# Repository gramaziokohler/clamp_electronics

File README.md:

# clamp_electronics
Electronics for remote controlled robotic actuators (clamps). 

This repo is part of the [Robotic Assembled Timber Structures with Integral Timber Joints](https://github.com/gramaziokohler/integral_timber_joints) project. 

## Repo folder structure

This repository hold the following files:

- **/xx_Description** - Eagle schematics and board designs for a specific controller design
- **/eagle_library** - stores custom eagle libraries from third-party or created by myself
- **/doc** - Electronics modules and other components documentation from original manufactures.

## Design Goals

The goal of the clamp controller is to be able to achieve the following high-level functions: 

- Communicate wirelessly with a radio base station
  - Receive commands
  - Report status
  - Report a jammed stop during move
- Control 1 or 2 motors for the clamp's main linear movement
  - Positional Control
  - Follow a trapezoidal motion profile
- Operate on 3 or 4-cell Li-Po Battery power
- Monitor jamming conditions of the clamp
- Monitor sensors (if any, such as loadcells)
- Monitor end / homing switch
- Monitor pneumatic autoswitch
- Monitor battery voltage

## Controller Design

Not all designs implemented the full list of design goals.

### [01_SerialController](/01_SerialController/01_SerialController.md)

This controller receives command from Serial Tx Rx pins.

Two load cell can be connected via two HX711 Analog-to_Digital Module.

The design supports two DC motors with *single* channel encoder. The shaft rotation direction is inferred from the direction of programmed movement. (This design is later proved to be imprecise)

### [02_RadioPIDController](02_RadioPIDController/02_RadioPIDController.md)

This controller interfaces the CC1101 radio directly via Hardware SPI on Arduino Nano. It can receive and respond to commands from either USB Serial or from the Radio.

The hardware and pin out supports two motors being PID controlled with two-channel encoder feedback.

### [03_RadioPIDControllerV2](03_RadioPIDControllerV2/03_RadioPIDControllerV2.md)

This controller is an improvement of the 02_RadioPIDController with the intent to improve the following aspects:

- Better DC power regulation to avoid digital blackout
- Ability to support a two-motor firmware or single-motor (with added features) firmware.
- 1 or 2 LED output with onboard series resistor

### [10_ESP32CAMAdapter](10_ESP32CAMAdapter/10_ESP32CAMAdapter.md)

This an adapter board for connecting AIThinker ESP32-CAM module.

## Sub-systems and Electronic Module Documentation

### Motor Driver

[Motor Driver XY160D](doc/motor_driver/motor_driver_XY160D.md)

This H-Bridge Bi-Directional MOSFET motor driver is chosen due to its high rated current (7A constant, 50A peak).  

- Other drivers such as L298N offers low output current (L298N only 2A constant output 3A peak per channel) 
- This driver has a simple IN1 + IN2 + ENA interface which is easy to interface. 
- PWM and Bidirectional operation is necessary for position control.

### Radio

[Details of CC1101 Radio Module](doc/radio/CC1101_Radio.md)

This CC1101 radio module is chosen because it is the most available sub-GHz packet based radio.

- The sub-GHz frequency is better at going around obstacles in a construction environment.
- ISM bands that are free to use.
- The highly integrated radio transceiver chip on a module is easy to use and interface. 
- Existing Arduino compatible library exists.

Radio frequency / channel / sync word and it's operation is controlled by software and are documented in firmware repo.

### MCU

The Arduino Nano (ATmega328 + new bootloader) is chosen for its small size, low cost and protoboard friendly pin layout. The Nano do not have a lot of IO available but is barely enough for a 2 motor controller.

[Arduino Nano V3 Pinout](http://lab.dejaworks.com/arduino-nano-pinouts/) ( [Arduino.cc Nano Page](https://store.arduino.cc/arduino-nano) )

### Load Cell

A 4-wire load cell can be used to dynamically measure the pull force of the actuator. Such load cell can be interfaced to the Arduino via a AD Converter designed for load cell measurement.

[Details of the HX711 Load Cell A/D Module](/doc/load_cell/load_cell.md)

The HX711 module was selected due to its compact size, low cost and ready-to-use library. Measuring frequency is 80Hz.

### Battery Voltage Regulation for controller

The fluctuating battery voltage for a 4-cell Li-Po is between 12.8V to 16.8V. This needs to be regulated to stable 5V DC for the digital circuitry.

[Details and calculation of LM7805 option](doc/voltage_regulation/linear_regulator.md)

### Battery Voltage Sense

[Details and calculation of voltage divider](doc/battery_sense/Battery_Voltage_Sensing.md)

### Battery Cable Harness

A Y cable is necessary to connect the Li-Po Battery to both the motor driver and the controller Battery. 

**Male XT60 Connector** at the battery side

**2x Female Phoenix Terminal Block Plug** (Phoenix 1757019 - MSTB 5.08 picth) at controller side.

------

## Peripheral Devices

The choice of DC motor and Li-Po Battery is flexible from the perspective of the controller electronics. As long as their specification is within allowable range defined below:

### DC Motor

The chosen DC motor should be rated 12V. Other ratings might work as long as overheat is not an issue and sufficient torque is produced.

### Hall Effect Sensor

Two phase hall effect shaft encoder should be used for positional feedback. The output of the encoder should ideally be 5V TTL logic. 

Should the motor have a gearbox, the shaft encoder should be attached to the motor shaft (not the gearbox output shaft) for better resolution.

Sensor resolution should be around 500 - 1000 steps per 1mm clamp linear output.

### Li-Po Battery

**4-cell** Li-Po battery is chosen for the following reasons:

- High power density for starting DC motor
- High energy density to save space and weight
- 14.8V - 16.8V voltage match well with 12V DC motor.

**1000mAh** or above for reasonable use time.

**XT60 Connector** is conventional

**Voltage Assumption for calculation**: We assume a fully charged 4-cell battery to have **16.8V (@4.2V)**, and stop using the battery at **14.8V (@3.7V)**  , although absolute minimum is **14.0V (@3.5V)**

Note: 3-cell battery will also operate fine but at reduced torque

Credits
-------------

This repository was created by Pok Yin Victor Leung <leung@arch.ethz.ch> [@yck011522 ](https://github.com/yck011522) at [@gramaziokohler](https://github.com/gramaziokohler)

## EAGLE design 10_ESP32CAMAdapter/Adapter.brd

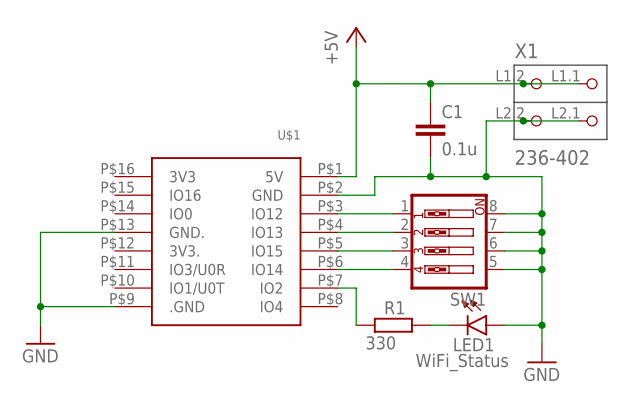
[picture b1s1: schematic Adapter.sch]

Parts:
C1: 0.1u; C050-030X075
LED1: WiFi_Status; LED3MM
R1: 330; 0204V
SW1: SW_DIP-4; EDG-04
U$1: ESP32-CAM
X1: 236-402; P-236-402

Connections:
+5V: C1.1, U$1.P$1 (5V), X1.L1.1 (P1.1), X1.L1.2 (P1.2)
GND: C1.2, LED1.A, SW1.5, SW1.6, SW1.7, SW1.8, U$1.P$2 (GND), U$1.P$9 (.GND), U$1.P$13 (GND.), X1.L2.1 (P2.1), X1.L2.2 (P2.2)
unnamed: SW1.1, U$1.P$3 (IO12)
unnamed: SW1.2, U$1.P$4 (IO13)
unnamed: SW1.3, U$1.P$5 (IO15)
unnamed: SW1.4, U$1.P$6 (IO14)
unnamed: R1.1, U$1.P$7 (IO2)
unnamed: LED1.K (C), R1.2

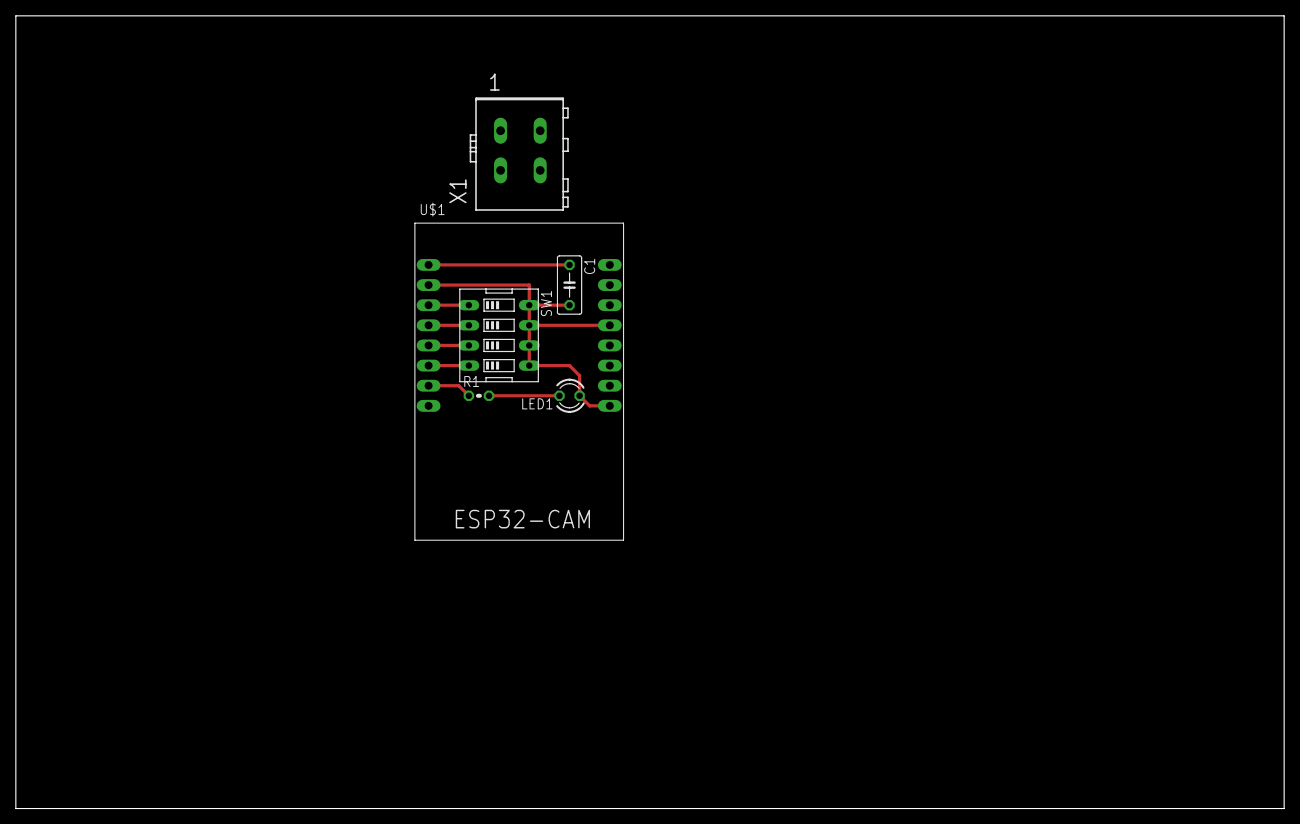
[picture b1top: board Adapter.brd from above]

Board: 2 copper layers, 160.0 x 100.0 mm, 6 parts (0 on the bottom side), 8 nets.

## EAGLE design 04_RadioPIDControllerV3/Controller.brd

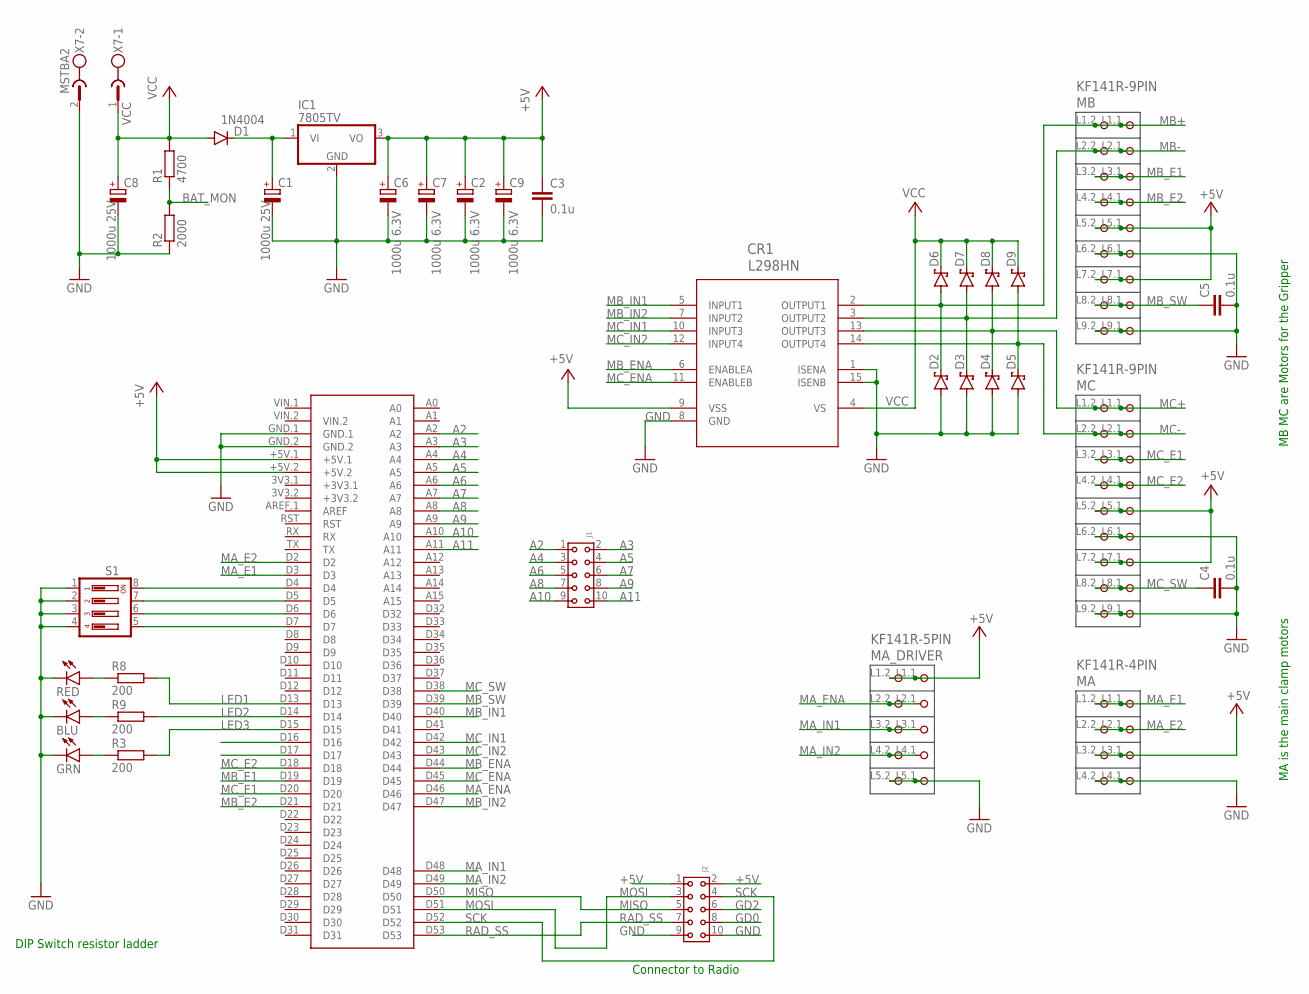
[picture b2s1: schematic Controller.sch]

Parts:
BLU: LED5MM
C1, C8: 1000u 25V; E3,5-10
C2, C6, C7, C9: 1000u 6.3V; E4-8-13HORI
C3, C4, C5: 0.1u; C050-030X075
CR1: L298HN; MULTIWATT15_H_STM
D1: 1N4004; DO41-10
D2, D3, D4, D5, D6, D7, D8, D9: 1N5819-B; DO41-7.6
GRN: LED5MM
IC1: 7805TV; TO220V
J1, J2: 6130XX21821_61301021821; 61301021821
MA: KF141R-4PIN
MA_DRIVER: KF141R-5PIN
MB: KF141R-9PIN
MC: KF141R-9PIN
R1: 4700; 0207/7
R2: 2000; 0207/7
R3, R8, R9: 200; 0207/7
RED: LED5MM
S1: DIP04YL
U$1: MEGA2560_MIKRO
X7: MSTBA2

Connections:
+5V: C2.+, C3.1, C6.+, C7.+, C9.+, CR1.9 (VSS), IC1.3 (VO), J2.1, J2.2, MA.L3.1 (P3.1), MA.L3.2 (P3.2), MA_DRIVER.L1.1 (P1.1), MA_DRIVER.L1.2 (P1.2), MB.L5.1 (P5.1), MB.L5.2 (P5.2), MB.L7.1 (P7.1), MB.L7.2 (P7.2), MC.L5.1 (P5.1), MC.L5.2 (P5.2), MC.L7.1 (P7.1), MC.L7.2 (P7.2), U$1.+5V.1, U$1.+5V.2
A2: J1.1, U$1.A2
A3: J1.2, U$1.A3
A4: J1.3, U$1.A4
A5: J1.4, U$1.A5
A6: J1.5, U$1.A6
A7: J1.6, U$1.A7
A8: J1.7, U$1.A8
A9: J1.8, U$1.A9
A10: J1.9, U$1.A10
A11: J1.10, U$1.A11
BAT_MON: R1.1, R2.2
GD0: J2.8
GD2: J2.6
GND: BLU.K (C), C1.-, C2.-, C3.2, C4.2, C5.2, C6.-, C7.-, C8.-, C9.-, CR1.1 (ISENA), CR1.8 (GND), CR1.15 (ISENB), D2.A, D3.A, D4.A, D5.A, GRN.K (C), IC1.2 (GND), J2.9, J2.10, MA.L4.1 (P4.1), MA.L4.2 (P4.2), MA_DRIVER.L5.1 (P5.1), MA_DRIVER.L5.2 (P5.2), MB.L6.1 (P6.1), MB.L6.2 (P6.2), MB.L9.1 (P9.1), MB.L9.2 (P9.2), MC.L6.1 (P6.1), MC.L6.2 (P6.2), MC.L9.1 (P9.1), MC.L9.2 (P9.2), R2.1, RED.K (C), S1.1, S1.2, S1.3, S1.4, U$1.GND.1, U$1.GND.2, X7.2
LED1: R8.2, U$1.D13
LED2: R9.2, U$1.D14
LED3: R3.2, U$1.D15
MA_E1: MA.L1.1 (P1.1), MA.L1.2 (P1.2), U$1.D3
MA_E2: MA.L2.1 (P2.1), MA.L2.2 (P2.2), U$1.D2
MA_ENA: MA_DRIVER.L2.1 (P2.1), MA_DRIVER.L2.2 (P2.2), U$1.D46
MA_IN1: MA_DRIVER.L3.1 (P3.1), MA_DRIVER.L3.2 (P3.2), U$1.D48
MA_IN2: MA_DRIVER.L4.1 (P4.1), MA_DRIVER.L4.2 (P4.2), U$1.D49
MB+: CR1.2 (OUTPUT1), D2.C, D6.A, MB.L1.1 (P1.1), MB.L1.2 (P1.2)
MB-: CR1.3 (OUTPUT2), D3.C, D7.A, MB.L2.1 (P2.1), MB.L2.2 (P2.2)
MB_E1: MB.L3.1 (P3.1), MB.L3.2 (P3.2), U$1.D19
MB_E2: MB.L4.1 (P4.1), MB.L4.2 (P4.2), U$1.D21
MB_ENA: CR1.6 (ENABLEA), U$1.D44
MB_IN1: CR1.5 (INPUT1), U$1.D40
MB_IN2: CR1.7 (INPUT2), U$1.D47
MB_SW: C5.1, MB.L8.1 (P8.1), MB.L8.2 (P8.2), U$1.D39
MC+: CR1.13 (OUTPUT3), D4.C, D8.A, MC.L1.1 (P1.1), MC.L1.2 (P1.2)
MC-: CR1.14 (OUTPUT4), D5.C, D9.A, MC.L2.1 (P2.1), MC.L2.2 (P2.2)
MC_E1: MC.L3.1 (P3.1), MC.L3.2 (P3.2), U$1.D20
MC_E2: MC.L4.1 (P4.1), MC.L4.2 (P4.2), U$1.D18
MC_ENA: CR1.11 (ENABLEB), U$1.D45
MC_IN1: CR1.10 (INPUT3), U$1.D42
MC_IN2: CR1.12 (INPUT4), U$1.D43
MC_SW: C4.1, MC.L8.1 (P8.1), MC.L8.2 (P8.2), U$1.D38
MISO: J2.5, U$1.D50
MOSI: J2.3, U$1.D51
unnamed: C1.+, D1.C, IC1.1 (VI)
unnamed: R8.1, RED.A
unnamed: BLU.A, R9.1
unnamed: GRN.A, R3.1
unnamed: S1.8, U$1.D4
unnamed: S1.7, U$1.D5
unnamed: S1.6, U$1.D6
unnamed: S1.5, U$1.D7
RAD_SS: J2.7, U$1.D53
SCK: J2.4, U$1.D52
VCC: C8.+, CR1.4 (VS), D1.A, D6.C, D7.C, D8.C, D9.C, R1.2, X7.1

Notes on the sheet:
Connector to Radio
DIP Switch resistor ladder
MB MC are Motors for the Gripper
MA is the main clamp motors

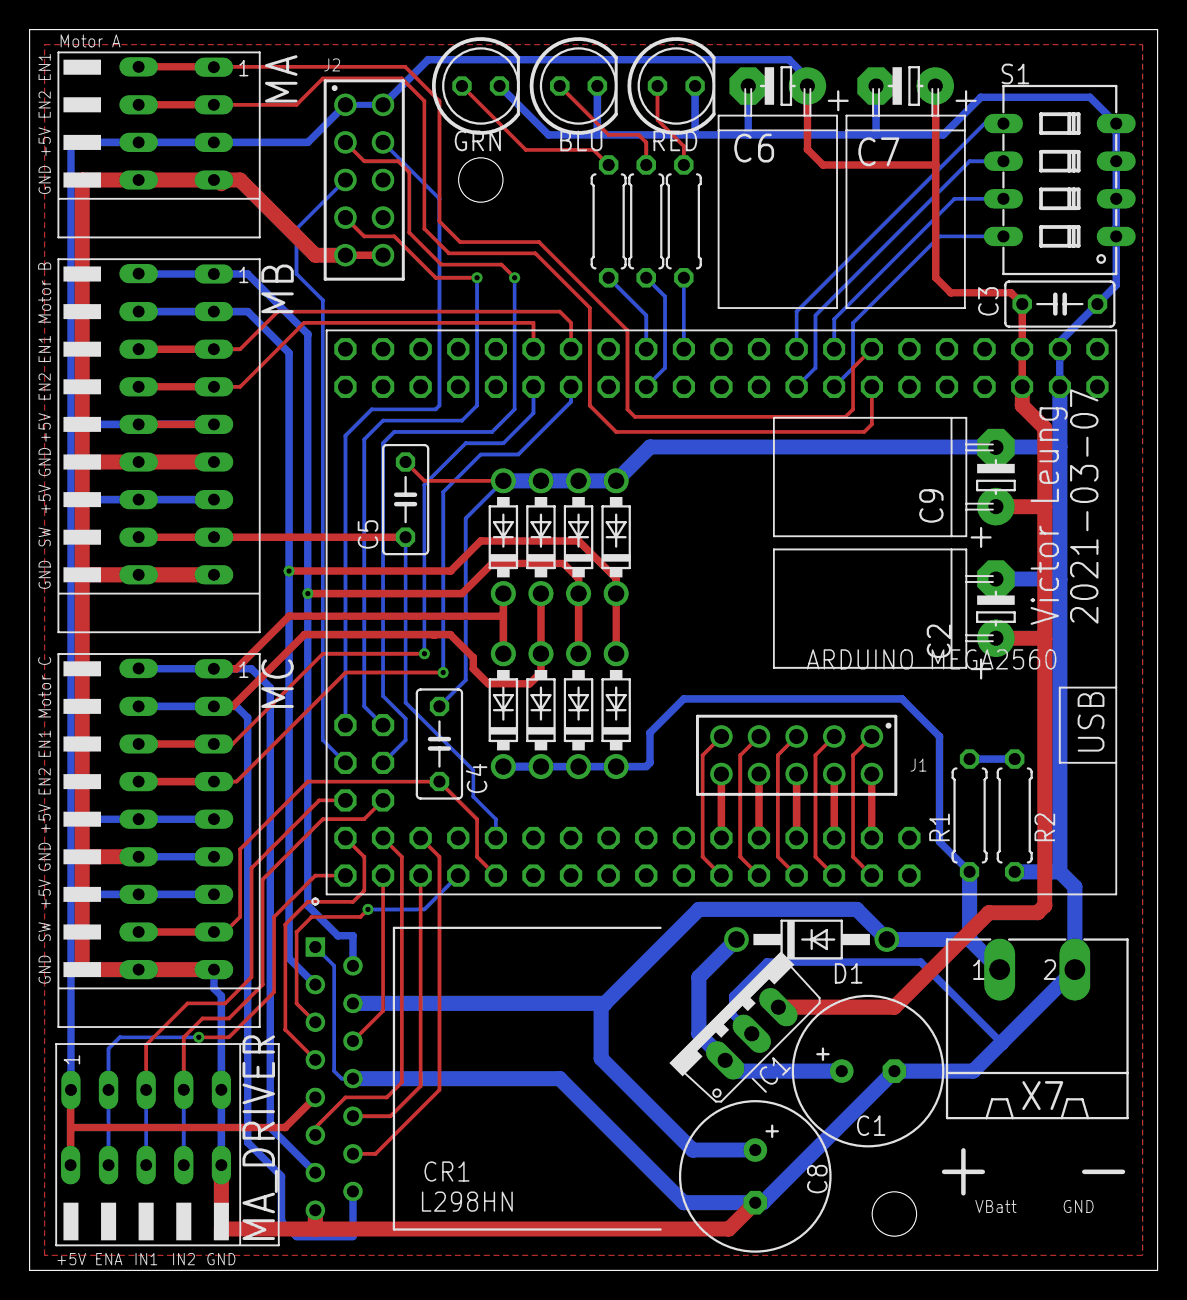
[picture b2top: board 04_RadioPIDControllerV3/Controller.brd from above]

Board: 2 copper layers, 76.2 x 83.8 mm, 37 parts (0 on the bottom side), 50 nets.

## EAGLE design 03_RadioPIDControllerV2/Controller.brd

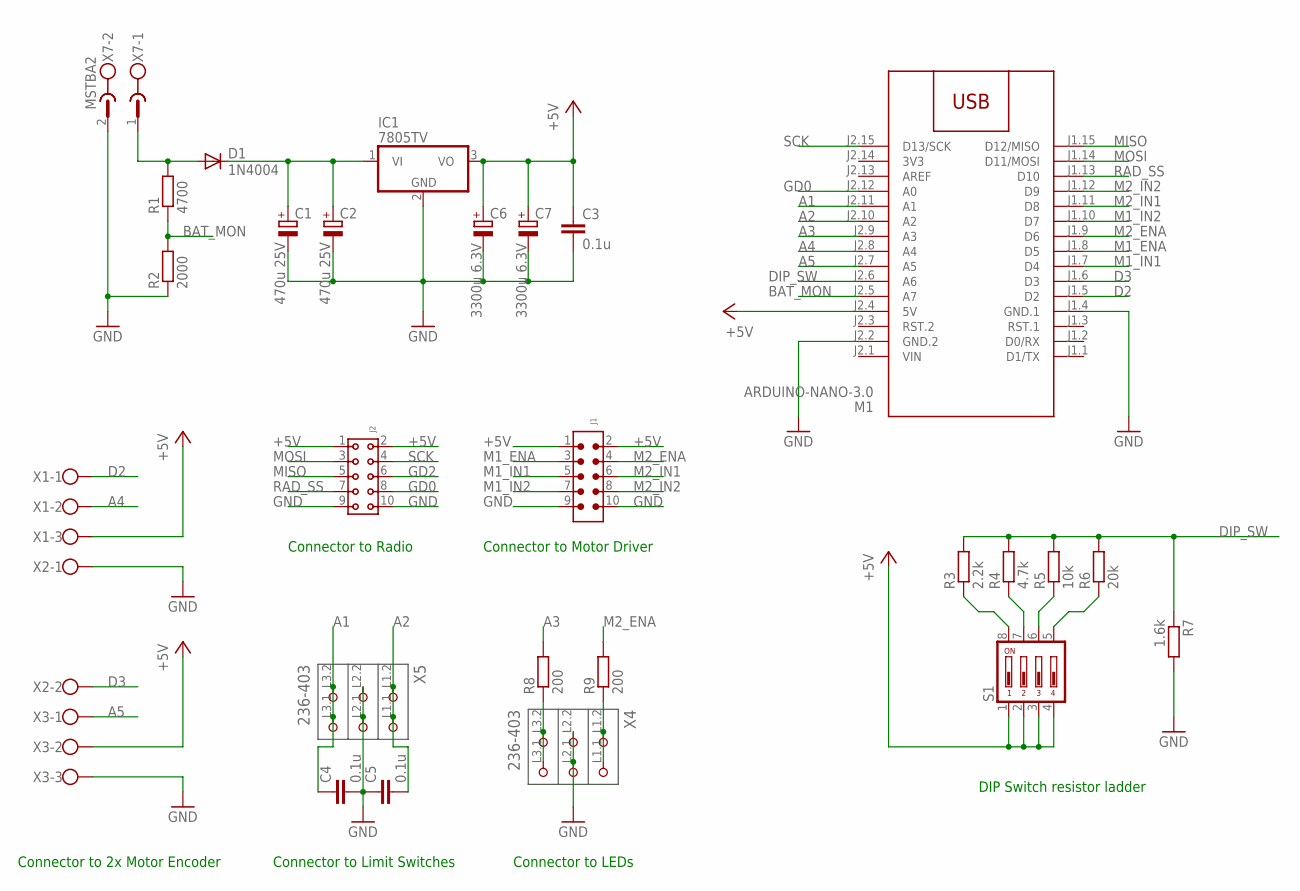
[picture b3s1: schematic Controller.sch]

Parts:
C1, C2: 470u 25V; E3,5-8
C3, C4, C5: 0.1u; C050-030X075
C6, C7: 3300u 6.3V; E3,5-10
D1: 1N4004; DO41-10
IC1: 7805TV; TO220V
J1: 6120XX21621_61201021621; 61201021621
J2: 6130XX21821_61301021821; 61301021821
M1: ARDUINO-NANO-3.0
R1: 4700; 0207/10
R2: 2000; 0207/7
R3: 2.2k; 0207/10
R4: 4.7k; 0207/10
R5: 10k; 0207/10
R6: 20k; 0207/10
R7: 1.6k; 0207/10
R8: 200; 0207/12
R9: 200; 0207/15
S1: DIP04YL
X1, X3: W237-103
X2: W237-102
X4, X5: 236-403; P-236-403
X7: MSTBA2

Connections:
3V3: M1.J2.14 (3V3)
+5V: C3.1, C6.+, C7.+, IC1.3 (VO), J1.1, J1.2, J2.1, J2.2, M1.J2.4 (5V), S1.1, S1.2, S1.3, S1.4, X1.3, X3.2
A1: C4.1, M1.J2.11 (A1), X5.L3.1 (P3.1), X5.L3.2 (P3.2)
A2: C5.2, M1.J2.10 (A2), X5.L1.1 (P1.1), X5.L1.2 (P1.2)
A3: M1.J2.9 (A3), R8.2
A4: M1.J2.8 (A4), X1.2
A5: M1.J2.7 (A5), X3.1
BAT_MON: M1.J2.5 (A7), R1.1, R2.2
D2: M1.J1.5 (D2), X1.1
D3: M1.J1.6 (D3), X2.2
DIP_SW: M1.J2.6 (A6), R3.2, R4.2, R5.2, R6.2, R7.1
GD0: J2.8, M1.J2.12 (A0)
GD2: J2.6
GND: C1.-, C2.-, C3.2, C4.2, C5.1, C6.-, C7.-, IC1.2 (GND), J1.9, J1.10, J2.9, J2.10, M1.J1.4 (GND.1), M1.J2.2 (GND.2), R2.1, R7.2, X2.1, X3.3, X4.L2.1 (P2.1), X4.L2.2 (P2.2), X5.L2.1 (P2.1), X5.L2.2 (P2.2), X7.2
M1_ENA: J1.3, M1.J1.8 (D5)
M1_IN1: J1.5, M1.J1.7 (D4)
M1_IN2: J1.7, M1.J1.10 (D7)
M2_ENA: J1.4, M1.J1.9 (D6), R9.2
M2_IN1: J1.6, M1.J1.11 (D8)
M2_IN2: J1.8, M1.J1.12 (D9)
MISO: J2.5, M1.J1.15 (D12/MISO)
MOSI: J2.3, M1.J1.14 (D11/MOSI)
unnamed: D1.A, R1.2, X7.1
unnamed: R8.1, X4.L3.1 (P3.1), X4.L3.2 (P3.2)
unnamed: C1.+, C2.+, D1.C, IC1.1 (VI)
unnamed: R4.1, S1.7
unnamed: R5.1, S1.6
unnamed: R6.1, S1.5
unnamed: R3.1, S1.8
unnamed: R9.1, X4.L1.1 (P1.1), X4.L1.2 (P1.2)
RAD_SS: J2.7, M1.J1.13 (D10)
SCK: J2.4, M1.J2.15 (D13/SCK)
VIN: M1.J2.1 (VIN)

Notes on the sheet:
Connector to Motor Driver
Connector to Radio
Connector to 2x Motor Encoder
DIP Switch resistor ladder
Connector to LEDs
Connector to Limit Switches

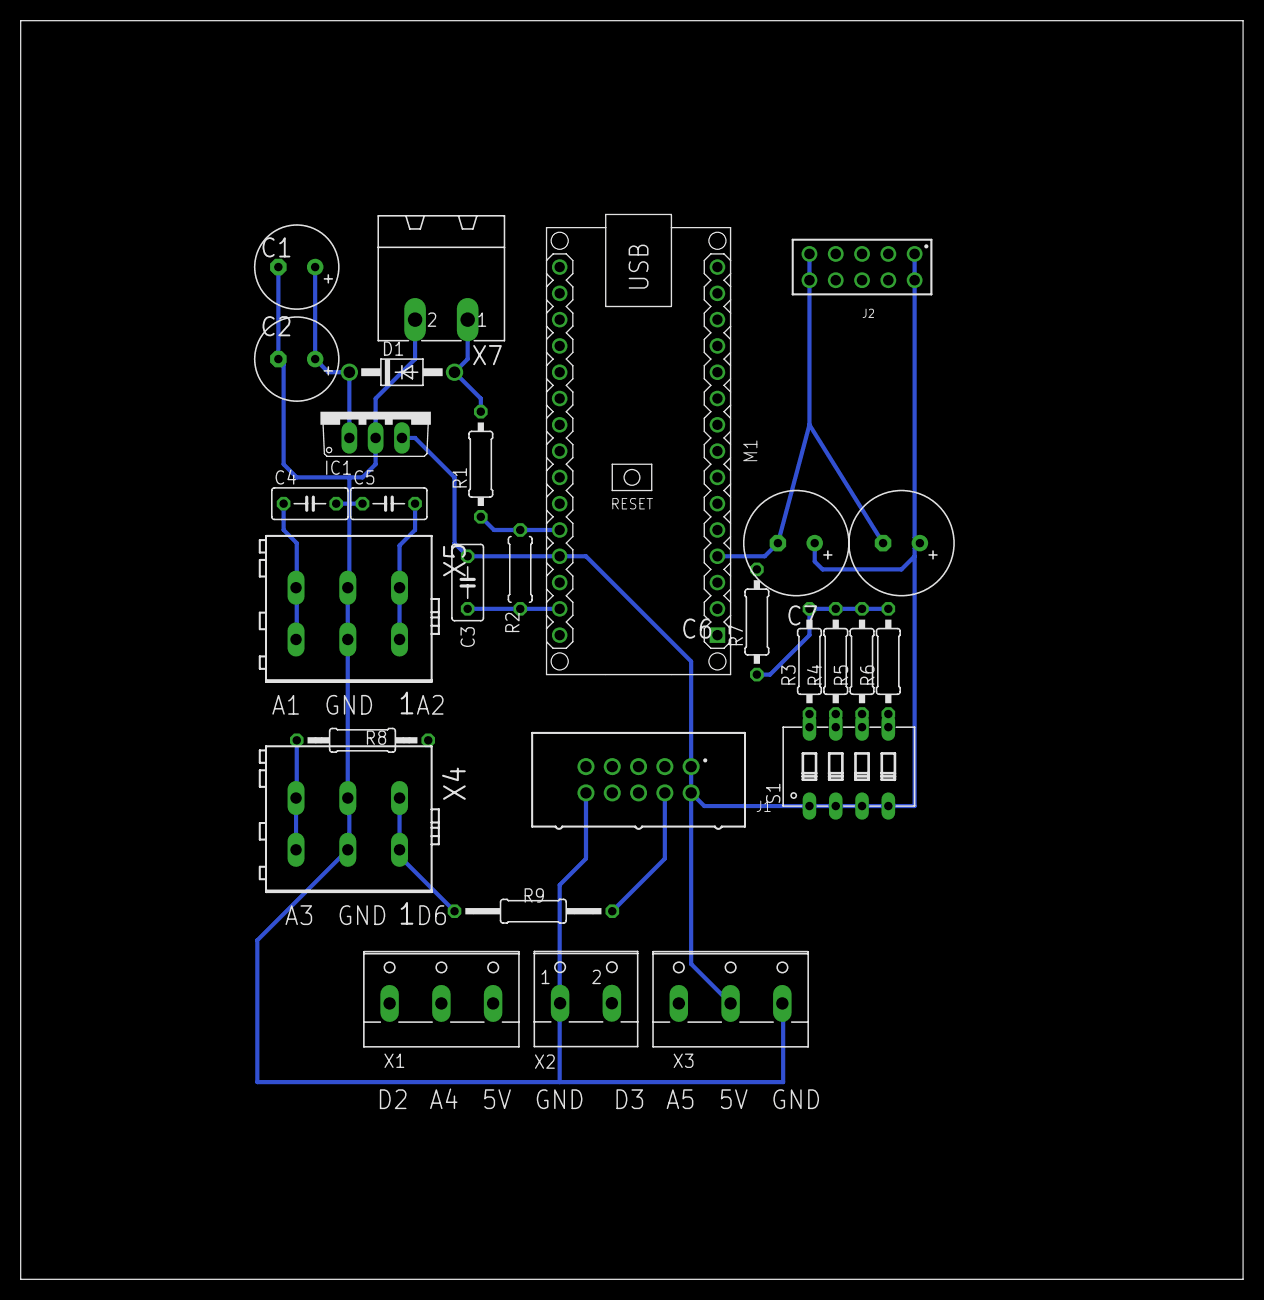
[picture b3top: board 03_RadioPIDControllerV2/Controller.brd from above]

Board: 2 copper layers, 118.1 x 121.6 mm, 28 parts (0 on the bottom side), 30 nets.

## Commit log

2020-04-10 Migrated a lot of docs to this repo
2020-04-11 Slash direction
2020-04-11 Doc for radio and controller 2
2020-04-11 New Line Problem
2020-04-11 Edited some note
2020-04-15 Plastic case
2020-04-16 Added Radio Dongle Doc
2020-04-16 Added photo to Controller 02
2020-04-16 Added Load cell Doc
2020-04-16 Added documentation for 01 Serial Controller
2020-04-16 Added some detail to 02 Controller doc
2020-06-28 Added Doc of Controller 03
2021-01-21 Case for the PID Controller board used for motor testing
2021-01-21 USB Dongle plastic case
2021-03-07 04 PID Controller with 2 extra motor
2021-05-01 png output
2021-05-01 Board error log
2021-10-18 Added Adapter board related to #2
2023-04-08 Updates documentation during thesis writing

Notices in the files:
parts and their libraries:
diy-modules: Released under the Creative Commons Attribution 4.0 International License: http://creativecommons.org/licenses/by/4.0
Wurth_Connectors_WR-BHD: Copyright: Würth Elektronik
